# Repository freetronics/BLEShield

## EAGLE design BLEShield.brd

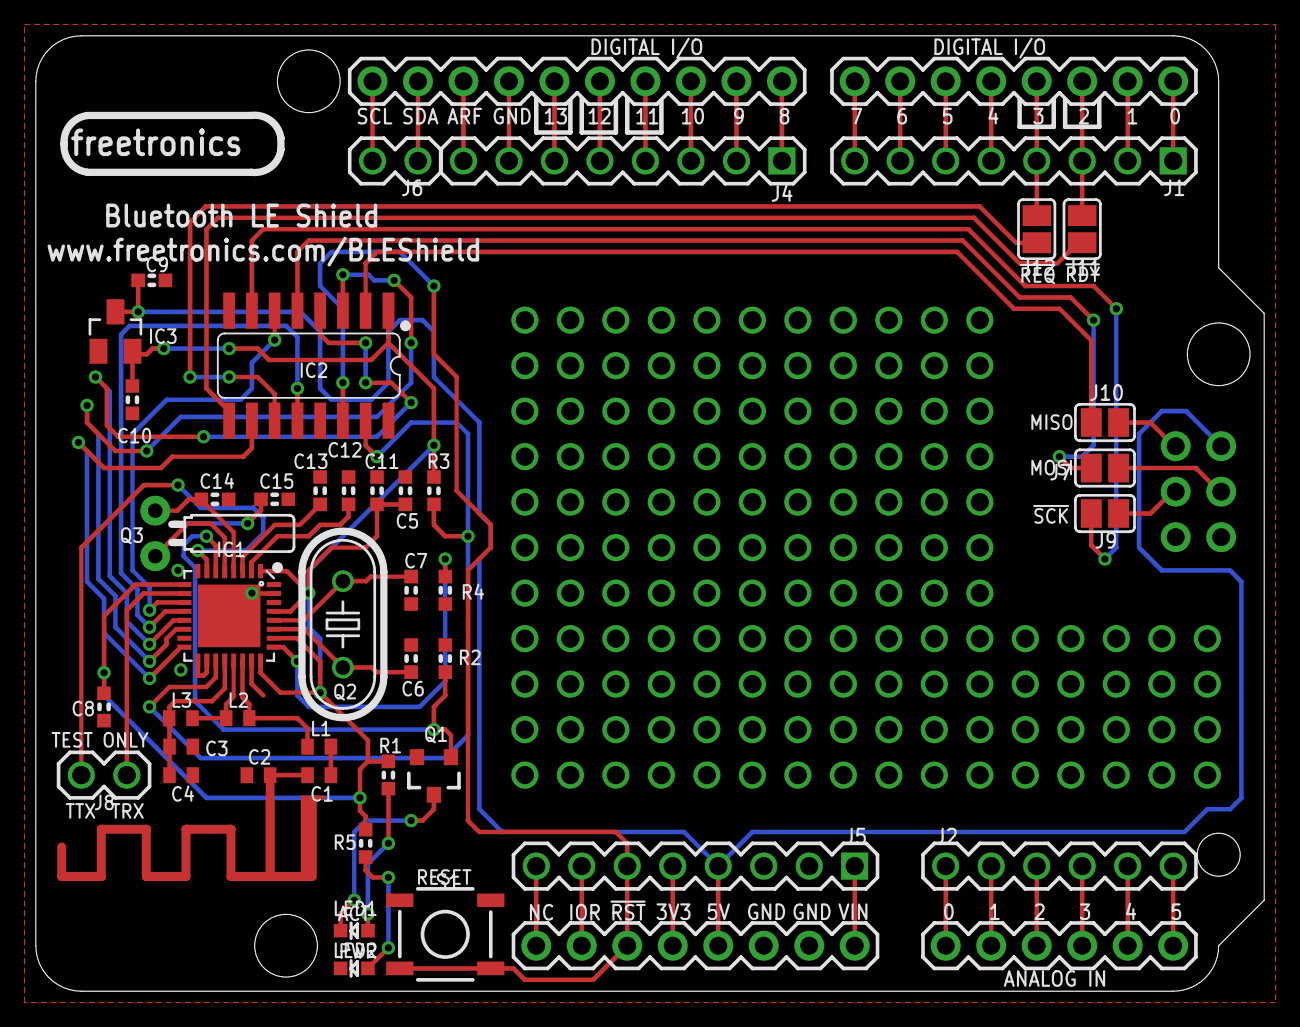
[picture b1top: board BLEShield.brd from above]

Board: 2 copper layers, 68.6 x 53.3 mm, 45 parts (0 on the bottom side), 63 nets.

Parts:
ANT1: ANTENNA; RN-ANT
C1: 1.8pF; C0402
C2: 1.2pF; C0402
C3: NP; C0402
C4: 2.2nF; C0402
C5: 1nF; 0603
C6, C7: 27pF; 0603
C8, C11, C12: 100nF; 0603
C9, C10: 1µF; 0603
C13: 33nF; 0603
C14, C15: 18pF; 0603
IC1: NRF8001; FITNESSDEVICE_QFN-32
IC2: HEF4050BT; SO16
IC3: MCP1700T-3002E; SOT23
J1, J4, J5: 1X08
J2: 1X06
J3: ARDUINO-SHIELD_R3
J6: 1X02
J7, J9, J10, J11, J12: SJ
J8: Debug/Test UART; 1X02
L1: 3.9nH; C0402
L2: 8.2nH; C0402
L3: 5.6nH; C0402
LED1: Activity; LED-0603
LED2: Power; LED-0603
Q1: 2N7002; SOT23-3
Q2: 16 MHz; HC49U-V
Q3: 32768 Hz; TC26H
R1, R5: 1kΩ; 0603
R2: 100kΩ; 0603
R3: 10kΩ; 0603
R4: 22kΩ 1%; 0603
S1: Reset; TACTILE_SWITCH_SMD

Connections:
!RDY: IC1.16, IC2.10
!REQ: IC1.12, IC2.12
!RESET: IC1.19, IC2.15, R3.2
!RESET_5V: IC2.14, J3.!RESET, J5.6, S1.3, S1.4
+3.0V: C5.2, C8.2, C10.2, C11.2, IC1.1, IC1.9, IC1.24, IC1.26, IC1.29, IC2.1, IC3.2, R1.1, R3.1, R5.2
+3.3V: J3.3V3, J5.5
+5V: C9.2, IC3.3, J3.+5V, J3.+5V@0, J5.4
A: IC2.5, J7.1
A0: J2.1, J3.A0
ACTIVE: IC1.6, Q1.1, R2.1
ANT1: IC1.21, L2.2, L3.1
ANT2: IC1.22, L1.2, L2.1
B: IC2.7, J9.1
C: IC2.9, J11.1
D: IC2.11, J12.1
D2: J1.3, J3.D2, J11.2
D3: J1.4, J3.D3, J12.2
GND: ANT1.GND, C2.1, C3.1, C4.1, C5.1, C6.1, C7.1, C8.1, C9.1, C10.1, C11.1, C12.1, C13.1, C14.1, C15.1, IC1.8, IC1.17, IC1.18, IC1.23, IC1.30, IC1.31, IC1.EP, IC2.8, IC3.1, J3.GND, J3.GND@0, J3.GND@1, J3.GND@2, J4.7, J5.2, J5.3, LED2.C, Q1.2, R2.2, R4.2, S1.1, S1.2
MISO: IC1.14, IC2.3
MISO_5V: J3.MISO, J10.2
MOSI: IC1.13, IC2.4
MOSI_5V: J3.MOSI, J7.2
unnamed: C12.2, IC1.2
unnamed: C13.2, IC1.3
unnamed: IC1.25, R4.1
unnamed: C7.2, IC1.28, Q2.1
unnamed: C6.2, IC1.27, Q2.2
unnamed: C14.2, IC1.4, Q3.1
unnamed: C15.2, IC1.5, Q3.2
unnamed: ANT1.FEED, C1.1, C2.2
unnamed: C1.2, L1.1
unnamed: LED2.A, R5.1
unnamed: LED1.C, Q1.3
unnamed: LED1.A, R1.2
unnamed: IC2.2, J10.1
unnamed: J2.2, J3.A1
unnamed: J2.3, J3.A2
unnamed: J2.4, J3.A3
unnamed: J2.5, J3.A4
unnamed: J2.6, J3.A5
unnamed: J3.RESERVED, J5.8
unnamed: J3.VIN, J5.1
unnamed: J3.IOREF, J5.7
unnamed: J1.1, J3.D0
unnamed: J1.2, J3.D1
unnamed: J1.5, J3.D4
unnamed: J1.6, J3.D5
unnamed: J1.7, J3.D6
unnamed: J1.8, J3.D7
unnamed: J3.SDA, J6.1
unnamed: J3.AREF, J4.8
unnamed: J3.D13, J4.6
unnamed: J3.D12, J4.5
unnamed: J3.SCL, J6.2
unnamed: J3.D8, J4.1
unnamed: J3.D9, J4.2
unnamed: J3.D10, J4.3
unnamed: J3.D11, J4.4
RXD: IC1.10, J8.1
SCK: IC1.11, IC2.6
SCK_5V: J3.SCK, J9.2
TXD: IC1.7, J8.2
VDD_PA: C3.2, C4.2, IC1.20, L3.2

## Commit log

2014-01-22 checked files are the right ones
2014-01-22 Moved traces to bottom layer near breakouts Relocated PCB to zero point Changed labels to vector font Increased label sizes Removed cut-track jumpers for SPI lines Converted remaining cut-track jumpe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
